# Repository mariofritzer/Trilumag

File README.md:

# Trilumag

Dreieckige RGBW-Lichtpanels zum Selberbauen, ähnlich wie Nanoleaf: Die Panels werden mit Magnet-Pogo-Steckern aneinandergeklipst, erkennen sich gegenseitig und erscheinen in der App genau so, wie sie an der Wand hängen. Gesteuert wird alles von einem ESP32 im Hauptpanel, per Web-App, HTTP-API und Home Assistant.

**Webinstaller:** https://mariofritzer.github.io/Trilumag/

## Stand

Aktuell: **Version 0.7**. Was sich wann geändert hat, steht im [Versionsverlauf](CHANGELOG.md).

Ab Version 0.2 gibt es zwei Betriebsarten, umschaltbar in der App: **Simulation** (Panels werden in der App per Ziehen angeklipst) und **Bus** (echte Panels über RS-485). Das Protokoll steht in [docs/protokoll.md](docs/protokoll.md).

| Teil | Stand |
| --- | --- |
| Firmware Hauptpanel (ESP32) | Simulation und echter Bus, Web-App im Stil von WLED mit fester Verbindung, Effekte mit Paletten, Presets, Pin-Einstellungen pro Board, MQTT mit Home-Assistant-Discovery, WLAN per Improv |
| Bus zu den Panels (RS-485) | Protokoll v1 fertig, am PC mit echter Firmware simuliert und getestet, Steckbrett-Test folgt |
| Firmware Panels (CH32V003) | Version 3: Erkennung, Farben, Kanten einzeln, Antippen per Bewegungssensor, Updates über den Bus mit eigenem Bootloader |
| Platinen | Entwurf v0.1 |

## Aufbau

- **Hauptpanel:** ESP32-S3, 24V-Eingang mit Sicherung und Verpolschutz, RS-485-Master, eigene LEDs
- **Panels:** CH32V003, RS-485, WS2814 24V RGBW (10 cm pro Kante)
- **Kanten:** je ein Paar Magnet-Pogo-Stecker (männlich + weiblich), 24V, GND, A, B und eine SNS-Leitung zur Nachbarerkennung
- **Kantennummerierung** bei jedem Panel gleich, gegen den Uhrzeigersinn: Kante 1 unten, 2 rechts, 3 links (Spitze oben)

## Ordner

| Ordner | Inhalt |
| --- | --- |
| `firmware/trilumag` | Arduino-Sketch für das Hauptpanel |
| `firmware/panel` | Firmware für die Panels (CH32V003, ch32fun) |
| `docs` | Bus-Protokoll |
| `installer` | Webinstaller-Seite (ESP Web Tools) |
| `.github/workflows` | baut die Firmware für ESP32, ESP32-S3, ESP32-C3 und ESP32-C6 und veröffentlicht den Installer |

## Selbst kompilieren

**Hauptpanel:** Arduino IDE mit dem Boardpaket **esp32** von Espressif, dazu die Bibliotheken **ArduinoJson** (ab 7), **PubSubClient** und **Adafruit NeoPixel**. Bei ESP32-S3, ESP32-C3 und ESP32-C6 unter Werkzeuge „USB CDC On Boot“ auf „Enabled“ stellen. Unter „Partition Scheme“ immer **Minimal SPIFFS (1.9MB APP with OTA)** wählen, sonst ist für Online-Updates kein Platz. Für den **ESP32-C6 mit Hue** zusätzlich „Zigbee mode“ auf **Zigbee ZCZR (coordinator/router)** stellen und `partitions_c6_zigbee.csv` als `partitions.csv` in den Sketch-Ordner kopieren (nur für diesen Build, sonst gilt sie für alle Chips). Die App steht in `webapp.h`; nach Änderungen daran `python3 .github/scripts/webapp_gz.py` ausführen, das erzeugt die gepackte Fassung `webapp_gz.h`, die das Hauptpanel ausliefert.

**Panels:** [ch32fun](https://github.com/cnlohr/ch32fun) und eine RISC-V-Toolchain. Ein neues Panel wird einmal mit dem WCH-LinkE programmiert: `make -C firmware/panel flashall CH32FUN=<pfad>/ch32fun/ch32fun` schreibt Bootloader, Option-Byte und Firmware. Danach bekommt es neue Versionen über den Bus vom Hauptpanel (Optionen → Panel-Firmware). Fertige Dateien gibt es bei jedem Release (`trilumag-panel.bin`, `trilumag-panel-bootloader.bin`).

## Web-App

Die App ist aufgebaut wie bei WLED: oben Ein/Aus und Gesamthelligkeit der ganzen Wand, unten fünf Tabs.

- **Farben:** Farbrad mit Helligkeit, Weißanteil, Schnellfarben und Hex-Eingabe. Ohne Auswahl gilt die Farbe für die ganze Wand. In der Vorschau oben angetippte Panels bekommen ihre eigene Farbe. Läuft ein Effekt, der eine Farbe benutzt, färbt das Farbrad den Effekt ein, statt ihn zu beenden.
- **Effekte:** Tempo, Intensität, Effektliste mit Suche und Paletten.
- **Wand:** Panels anordnen (in der Simulation per Ziehen), Details, Helligkeit und Ein/Aus pro Panel.
- **Presets:** Szenen speichern, abrufen und löschen (bis zu 16).
- **Optionen:** WLAN (gefundene Netze zum Antippen), Betriebsart, Board und Pins, Farbreihenfolge mit Farbtest, MQTT mit Schalter „MQTT aktiv“.

Die App hält wie WLED eine feste Verbindung (WebSocket auf Port 81). Das Hauptpanel schickt Änderungen und das Effektbild etwa 15-mal pro Sekunde von selbst. Ist die Verbindung weg, fragt die App per HTTP nach, bis sie wieder steht.

Updates über den Webinstaller behalten WLAN, Einstellungen, Farben und Presets. Nur „Gerät löschen“ beim Installieren setzt alles zurück.

## Android-App

Die App hat eine eigene Versionsnummer (1.0, 1.1, …), unabhängig von der Firmware; sie steigt nur, wenn sich an der App etwas ändert. Die Datei heißt `trilumag-app-<Version>.apk` und hängt an dem Release, mit dem diese App-Version kam: <https://github.com/mariofritzer/Trilumag/releases>. Beim ersten Installieren fragt Android, ob der Browser Apps installieren darf; das einmal erlauben.

- Beim Start sucht die App alle Trilumag im WLAN und zeigt sie als Liste mit Namen, Farbe, Ein/Aus-Schalter und Helligkeitsregler, ähnlich wie die WLED-App.
- Antippen öffnet die gewohnte Steuerung im Vollbild. ＋ fügt eine Wand über ihre IP-Adresse hinzu, langes Drücken entfernt sie aus der Liste.
- Die App sieht selbst bei GitHub nach (höchstens alle drei Stunden) und zeigt oben einen Hinweis, wenn eine neuere App-Version da ist. „Installieren“ lädt sie in der App herunter und installiert sie; dahinter wird alles unscharf, davor stehen Fortschritt und der aktuelle Schritt. Beim ersten Mal fragt Android, ob Trilumag Apps installieren darf.
- Sicherungen und das Wandbild werden unter Downloads gespeichert.
- **Hinweis bei Störung** (unten in der Liste einschalten): Die App sieht etwa alle 15 Minuten im Hintergrund nach, ob alle Panelwände erreichbar sind und ihre Panels antworten, und meldet sich sonst. Nur im eigenen WLAN, unterwegs kommt nichts.

## Effekte und Paletten

Effekte laufen immer über die ganze Wand: Einfarbig, Regenbogen, Regenbogenwelle, Atmen, Farbwechsel, Funkeln, Ausbreiten (Wellen vom Hauptpanel nach außen), Feuer und Polarlicht. Die **Intensität** ändert je nach Effekt die Streuung, die Tiefe des Atmens, wie oft es funkelt, die Breite der Wellen oder wie stark das Feuer flackert.

**Paletten:** Standard (die eigenen Farben des Effekts), Regenbogen, Effektfarbe, Ozean, Lava, Wald, Sonnenuntergang, Party, Pastell und Eis.

Das Hauptpanel rechnet die Bilder selbst und schickt etwa 25 pro Sekunde mit einem FRAME-Befehl an alle Panels. Neu angeklipste Panels pulsieren erst 5-mal blau (etwa 8 Sekunden) und laufen dann mit. Bekommt ein einzelnes Panel eine feste Farbe, endet der Effekt. Der zuletzt gewählte Effekt läuft nach einem Neustart weiter.

## Presets

Ein Preset merkt sich Ein/Aus, Gesamthelligkeit, den Effekt mit Tempo, Intensität, Palette und Effektfarbe und die Farbe jedes bekannten Panels über seine Chip-ID. Ist ein Panel beim Laden gerade nicht an der Wand, bekommt es seine Farbe beim nächsten Anklipsen.

## Home Assistant

In der App unter Optionen „MQTT aktiv“ einschalten und die Adresse des Brokers eintragen. Danach erscheinen automatisch:

- **Ein Licht pro Panel**
- **„Alle Panels“:** Ein/Aus, Gesamthelligkeit, Farbe und die Effektliste.
- **Schieberegler:** „Effekt-Tempo“ und „Effekt-Intensität“.
- **Auswahlen:** „Palette“ und „Preset“.
- **Status** (Diagnose): „Bereit“ oder „Update läuft“. Während die Wand eine neue Firmware installiert, trennt sie alle Verbindungen nach außen (MQTT, Hue, WLED, Wetter, Suche nach anderen Wänden) und verbindet sich nach dem Neustart von selbst wieder.

## Signale und Fortschritt (Home Assistant)

- **Signal:** Das Gerät „Signal“ (notify) lässt die ganze Wand blinken, danach läuft alles weiter wie vorher, auch ein Effekt. Nachricht: Farbe und Anzahl, z. B. `blau 3` oder `#ff8800 5`. Farben: rot, grün, blau, gelb, orange, lila, pink, türkis, weiß.

  ```yaml
  action: notify.send_message
  target: {entity_id: notify.trilumag_signal}
  data: {message: "blau 3"}
  ```

  Per MQTT geht auch JSON an `trilumag/signal/set`: `{"color":"grün","blink":2,"ms":700}`.
- **Fortschritt:** Die Zahl „Fortschritt“ (0 bis 100 %) füllt die Wand vom Hauptpanel aus, 0 % schaltet es aus. Mit Farbe per MQTT an `trilumag/fortschritt/set`: `{"value":40,"color":"grün"}`.

## Mehrere Wände

Unter Optionen → Mehrere Wände lassen sich Wände im selben WLAN zu einer Gruppe (1 bis 9) verbinden. Sie teilen Ein/Aus, Helligkeit und Effekt mit allen Einstellungen, egal an welcher Wand man etwas ändert. Den Takt der Effekte gibt die Wand mit der kleinsten Chip-ID vor. Feste Farben einzelner Panels bleiben pro Wand.

## Energie

Trilumag zählt den Verbrauch mit, gemessen mit dem INA226 oder aus den Farben geschätzt, und zeigt ihn unter Optionen → Energie pro Tag, Monat und Jahr. Das Datum kommt per Internet (NTP, Zeitzone Österreich). In Home Assistant gibt es den Zähler „Energie“ (kWh) für das Energie-Dashboard.

## WLAN-Wächter und Neustart-Grund

Unter Optionen → WLAN lässt sich der WLAN-Wächter ein- und ausschalten (Standard: an). Ist das WLAN 3 Minuten weg, verbindet sich Trilumag neu; fehlt es nach 10 Minuten immer noch, startet es neu, außer jemand ist gerade im Setup-Netz. Hängt die Hauptschleife eine Minute, startet es ebenfalls neu. `trilumag.local` wird alle 30 Minuten neu angekündigt. Warum Trilumag zuletzt neu gestartet ist (Stromausfall, Update, Absturz, Wächter …) und wie oft es abgestürzt ist, steht unter Optionen → Info und im Ereignisprotokoll.

## Andere Trilumag im WLAN

Unter Optionen → Andere Trilumag sucht die App nach weiteren Wänden im selben WLAN (per mDNS) und listet sie mit Name, Adresse und Version auf. „Öffnen“ führt direkt zu deren Steuerungsseite. Laufen mehrere Wände, heißt nur eine davon `trilumag.local`, die anderen bekommen automatisch `trilumag-2.local` und so weiter; die Liste zeigt, welche welche ist.

Unter Optionen → Updates lässt sich dann auswählen, auf welchen Wänden eine Version installiert wird: diese Wand und/oder gefundene andere. Die anderen holen sich die Version selbst von GitHub; ist diese Wand auch dabei, kommt sie zuletzt dran. Wände ab 0.7.21 lassen sich so aktualisieren.

## Raum: mehrere Panelwände zusammen

Begriffe: Eine **Panelwand** ist ein Trilumag mit seinen Panels, eine **Raumwand** eine Wand des Raums im Grundriss.

Unter Optionen → Andere Trilumag → „Raum einrichten“ (in der Android-App über ⌂ oben):

- **Grundriss von oben:** Ecken ziehen, ＋ an einer Raumwand fügt eine Ecke ein, eine Ecke oder Raumwand antippen zum Löschen. Die Panelwände (Striche) zieht man entlang der Raumwände an ihren Platz.
- **Jede Raumwand von vorne:** so, wie man im Raum davor steht, mit den echten Panel-Formen und ihren aktuellen Farben. Panelwände frei an ihre Stelle und Höhe ziehen.
- **Maße:** Raumhöhe und Seitenlänge eines Panels in cm.
- Der Raum liegt auf allen Panelwänden gleich: wo man ihn ändert, wird er an alle anderen weitergegeben. Klipst man an einer Panelwand Panels ab oder an, zieht sie ihren Eintrag selbst nach.
- **Raum-Effekte:** Der Raum-Komet läuft wie der Komet einer Panelwand: Panel für Panel, bei „Kanten einzeln“ Kante für Kante, und springt am Ende einer Panelwand zur nächsten Panelwand im Raum. Es gibt genau einen Kopf für alle Panelwände. Raum-Regenbogen und Raum-Welle laufen entlang der Raumwände über alle Panelwände. Jede Panelwand rechnet selbst mit ihrer Stelle im Raum und der Uhrzeit aus dem Internet, es werden keine Bilder verschickt. Lange Lücken zwischen den Panelwänden werden dabei kurz. Helligkeit, Tempo, Intensität und Palette gehen an alle Panelwände, eigene Paletten mit ihren Farben.
- **Mehrere Räume** (bis zu 6): oben im Raum-Fenster umschalten, „＋ Raum“ legt einen neuen an, der Name steht unter „Maße“. Eine Panelwand steht in höchstens einem Raum; „Hierher holen“ holt sie aus einem anderen.
- **Raum löschen:** löscht diesen Raum mit Grundriss, Aufstellung und Szenen auf allen Panelwänden; die Panelwände und ihre Einstellungen bleiben.
- **Raum-Szenen:** merken sich, was jede Panelwand im Raum zeigt (Effekt, Farben, Helligkeit), und stellen es auf allen wieder her (bis zu 8 je Raum).
- **Antippen:** Steht die Panelwand in einem Raum, läuft die Welle beim Antippen über alle Panelwände des Raums.
- **Home Assistant:** Jeder Raum erscheint als eigenes Licht (Ein/Aus, Helligkeit, alle Effekte inkl. Raum-Effekte) für alle seine Panelwände.
- **Weitere Raum-Effekte:** Raum-Feuerwerk (Raketen explodieren an Panels im ganzen Raum), Raum-Pingpong (ein Lichtpunkt springt zwischen den Panelwänden hin und her), Raum-Atmen (Atmen als Welle von der Mitte durch den Raum).
- Die anderen Panelwände brauchen dafür mindestens dieselbe Version.

Auch der Gleichtakt (unter „Mehrere Panelwände“) nimmt jetzt eigene Paletten mit ihren Farben mit; die andere Panelwand legt sie als „mitgenommene“ Palette ab, ohne ihre eigenen zu ändern.

## Weißton und Tageslicht-Kurve

Im Tab Farben stellt der Regler „Weißton“ Weiß zwischen 2200 K (warm) und 6500 K (kalt) ein; Home Assistant bekommt dafür den Farbtemperatur-Modus. Unter Optionen → Licht macht die „Tageslicht-Kurve“ alle Farben und Effekte abends wärmer und dunkler (ab 18 Uhr, nachts ganz warm auf 35 %, ab 6 Uhr wieder hell). Die Uhrzeit kommt per Internet.

## Eigene Paletten

Im Tab Effekte unter „Eigene Paletten“ lassen sich bis zu 4 Paletten mit 2 bis 6 Farben anlegen (als Vorlage gibt es „Rot-Gold-Weiß“). Sie stehen in der Palettenliste, in Home Assistant und in Presets wie die eingebauten.

## Wetter

Der Effekt „Wetter“ zeigt die Außentemperatur als Farbe (blau = kalt, gelb = mild, rot = heiß), bei Regen laufen blaue Tropfen über die Wand, bei Schnee weiße. Den Ort trägst du unter Optionen → Wetter ein; die Daten kommen alle 15 Minuten von Open-Meteo, kostenlos und ohne Anmeldung.

## Spiel „Simon sagt“

Unter Wand → Spiel startet ein Merkspiel: Die Wand zeigt eine Folge von Panels, man tippt sie nach, jede Runde kommt eines dazu. Dafür muss „Panels reagieren auf Antippen“ an sein, und es braucht mindestens zwei Panels mit Sensor. Der Rekord wird gespeichert.

## WLED nachahmen

Unter Optionen → WLED nachahmen findet die App WLED-Geräte im WLAN (oder man gibt die IP ein). Trilumag fragt das Gerät alle 1,5 s ab und übernimmt Änderungen an Ein/Aus, Helligkeit, Farbe, Tempo und Intensität, dazu den Effekt, wenn es ein Gegenstück gibt (etwa Rainbow, Breathe, Fire 2012, Aurora, Sparkle, Meteor, Lightning, Fireworks).

## Hue-Lampe nachahmen

Unter Optionen → Hue-Lampe nachahmen folgt die Wand einer Lampe der Hue Bridge (geht mit jedem Chip, übers WLAN): Bridge suchen, den runden Knopf auf der Bridge drücken und „Koppeln“ tippen, dann eine Lampe wählen. Trilumag fragt die Lampe jede Sekunde über die lokale Schnittstelle der Bridge (API v2) ab und übernimmt Ein/Aus, Helligkeit, Farbe, Weißton und die Effekte Kerze, Feuer, Funkeln, Prisma und Opal.

## Störungsanzeige

Ist das WLAN weg oder antwortet ein Panel nicht mehr, blinkt das Hauptpanel alle 10 Sekunden zweimal kurz (orange bzw. rot), solange die Wand an ist. Abschaltbar unter Optionen → WLAN.

## Wand als Bild

Unter Wand → „Wand als Bild speichern“ entsteht ein PNG mit den aktuellen Farben, Panelnummern, Chip-IDs, der Ausrichtung (Punkt = Kante 1) und den Datenverbindungen.

## Panel tauschen

In der App unter Wand das Panel antippen und „Tauschen“ wählen. Danach bleiben 5 Minuten Zeit: das alte Panel abklipsen und das neue an genau dieselbe Stelle setzen. Das neue übernimmt Farbe, Helligkeit und „Kanten einzeln“ des alten. Solange läuft unten in der App ein kleines Fenster mit der Restzeit und ✕ zum Abbrechen. Panels, die hinter dem alten hingen, gehen beim Abklipsen kurz aus und melden sich über das neue wieder; in der Simulation landen sie dazwischen in der Ablage und kommen danach von selbst an ihren Platz zurück.

## Sprache

Die App ist auf Deutsch und Englisch. Sie richtet sich nach der Sprache des Browsers; unter Optionen → Name lässt sie sich fest einstellen. Die Namen in Home Assistant und die Versionshinweise bleiben deutsch.

## Philips Hue (nur ESP32-C6)

Mit einem ESP32-C6 als Hauptpanel meldet sich Trilumag zusätzlich als Zigbee-3.0-Farblampe „Trilumag Wand“. Eine Hue Bridge (auch die Bridge Pro) nimmt sie wie eine Lampe eines anderen Herstellers auf: Ein/Aus, Helligkeit und Farbe der ganzen Wand, auch in Szenen, Routinen und mit Hue-Schaltern. Effekte und einzelne Panels bleiben in der Trilumag-App.

- Einschalten unter Optionen → Philips Hue, dann in der Hue-App unter Einstellungen → Lampen → „+“ nach neuen Lampen suchen.
- Der C6 braucht dafür einmal die neue Speicheraufteilung mit den Zigbee-Bereichen: einmal mit dem Webinstaller flashen. Einstellungen und Wand bleiben erhalten.
- WLAN und Zigbee teilen sich beim C6 eine Antenne. Hängt das Hauptpanel mit Zigbee dreimal beim Start, schaltet es Zigbee von selbst wieder aus.
- Alle anderen Chips haben kein Zigbee, dort fehlt das Kästchen in der App.

## API

| Aufruf | Zweck |
| --- | --- |
| `GET /api/state` | alle Panels mit Position, Drehung und Farbe, dazu Ein/Aus, Gesamthelligkeit, Effekt, Effekte, Paletten und Presets |
| `POST /api/set` | ein Panel: `{"id":"A3F2C1D0","state":"ON","brightness":180,"color":{"r":255,"g":0,"b":0,"w":0}}`, mehrere: `{"ids":[…],…}`, ganze Wand: `{"id":"alle","state":"ON","brightness":200,"color":{…}}` (hier ist `brightness` die Gesamthelligkeit), Helligkeit aller Panels: `{"panelBri":255}`, Weißton: `"kelvin":2700` statt `color` |
| `POST /api/effect` | `{"effect":"welle","speed":50,"intensity":128,"palette":"ozean","direction":90,"spin":0}`, alle Felder optional, `"aus"` heißt Einfarbig. Beim Farbverlauf (`"verlauf"`) setzt `"color2":{"r":0,"g":80,"b":255,"w":0}` die zweite Farbe |
| `POST /api/presets` | `{"action":"save","name":"Abend"}`, `{"action":"load","id":0}`, `{"action":"delete","id":0}` |
| `GET /api/live` | aktuelles Effektbild aller Panels als RRGGBBWW |
| `GET /api/diag` | Bus-Diagnose: Zähler, Antwortzeiten pro Panel, Ereignisprotokoll |
| `GET /api/backup`, `POST /api/restore` | Sicherung herunterladen und einspielen |
| `POST /api/light` | Übergangszeit, Stromlimit und Stromsensor-Pins |
| `POST /api/touch` | Antippen: an/aus, Empfindlichkeit 1–10, Aktion für einmal (`a1`) und doppelt (`a2`) |
| `POST /api/signal` | Signal: `{"color":"blau","blink":3,"ms":700}` |
| `POST /api/progress` | Fortschritt: `{"value":40,"color":"grün"}`, `0` = aus |
| `POST /api/identify` | Panel finden: `{"id":"…"}`, das Panel blinkt 3 s weiß |
| `POST /api/favs` | Favoriten: `{"effect":"lava","on":true}` |
| `POST /api/swap` | Panel tauschen: `{"id":"altes Panel"}` startet, danach 5 Minuten Zeit; `{"stop":true}` bricht ab |
| `POST /api/ota` | Updates: `{"action":"check"}`, `{"action":"install","version":"0.7.40"}`, auch für andere Wände: `"peers":["192.168.1.61"]`, ohne diese Wand: `"self":false` |
| `POST /api/peers`, `GET /api/peers` | andere Trilumag im WLAN suchen (dauert etwa 3 s) und die Liste abholen |
| `POST /api/palette` | Eigene Palette: `{"action":"save","slot":0,"name":"Rot-Gold-Weiß","colors":["#FF0000","#FFB000","#FFFFFF"]}`, `{"action":"delete","slot":0}` |
| `POST /api/weather` | Wetter: `{"place":"Wien"}` (Ort suchen und Wetter holen), `{"place":""}` löscht ihn |
| `POST /api/game` | Spiel „Simon sagt“: `{"action":"start"}` / `{"action":"stop"}` |
| `POST /api/hue`, `GET /api/hue` | Hue-Lampe nachahmen: `{"action":"find"}`, `{"action":"pair"}`, `{"action":"lights"}`, `{"action":"follow","id":"…","name":"…"}`, `{"action":"stop"}`, `{"action":"forget"}`; GET liefert Bridges und Lampen |
| `POST /api/mirror` | WLED nachahmen: `{"ip":"192.168.1.70"}`, `{"ip":""}` beendet es |
| `POST /api/fault` | Störungsanzeige: `{"on":true}` |
| `POST /api/guard` | WLAN-Wächter: `{"on":true}` |
| `POST /api/sleep` | Sleep-Timer: `{"min":30}`, `0` beendet ihn |
| `POST /api/boot` | Nach Stromausfall: `{"mode":0}` wie vorher, `1` aus, `2` an, `3` mit `"preset"` |
| `GET /api/energy` | Energieverbrauch: heute, Monat, Jahr, gesamt und Werte pro Tag, Monat und Jahr (Wh) |
| `POST /api/sync` | Mehrere Wände im Gleichtakt: `{"on":true,"group":1}` (UDP-Port 21330 im WLAN) |
| `POST /api/zigbee` | Nur ESP32-C6: `{"action":"on","value":true}` (startet neu), `{"action":"pair"}` (neu koppeln) |
| `POST /api/panelfw` | Panel-Firmware: `{"action":"all"}`, `{"action":"one","id":"…"}`, `{"action":"auto","on":true}` |
| `/json`, `/json/state`, `/json/info`, `/presets.json` | WLED-kompatible Schnittstelle (eine Wand = ein Segment) |
| `POST /api/sim/attach` | Simulation: Panel anklipsen |
| `POST /api/sim/detach` | Simulation: Panel abklipsen |
| `POST /api/sim/rotate` | Simulation: Panel an Ort und Stelle drehen, `{"id":"…"}` |
| `POST /api/sim/remove` | Simulation: Panel aus der Ablage löschen, `{"id":"…"}` oder `{"all":true}` |

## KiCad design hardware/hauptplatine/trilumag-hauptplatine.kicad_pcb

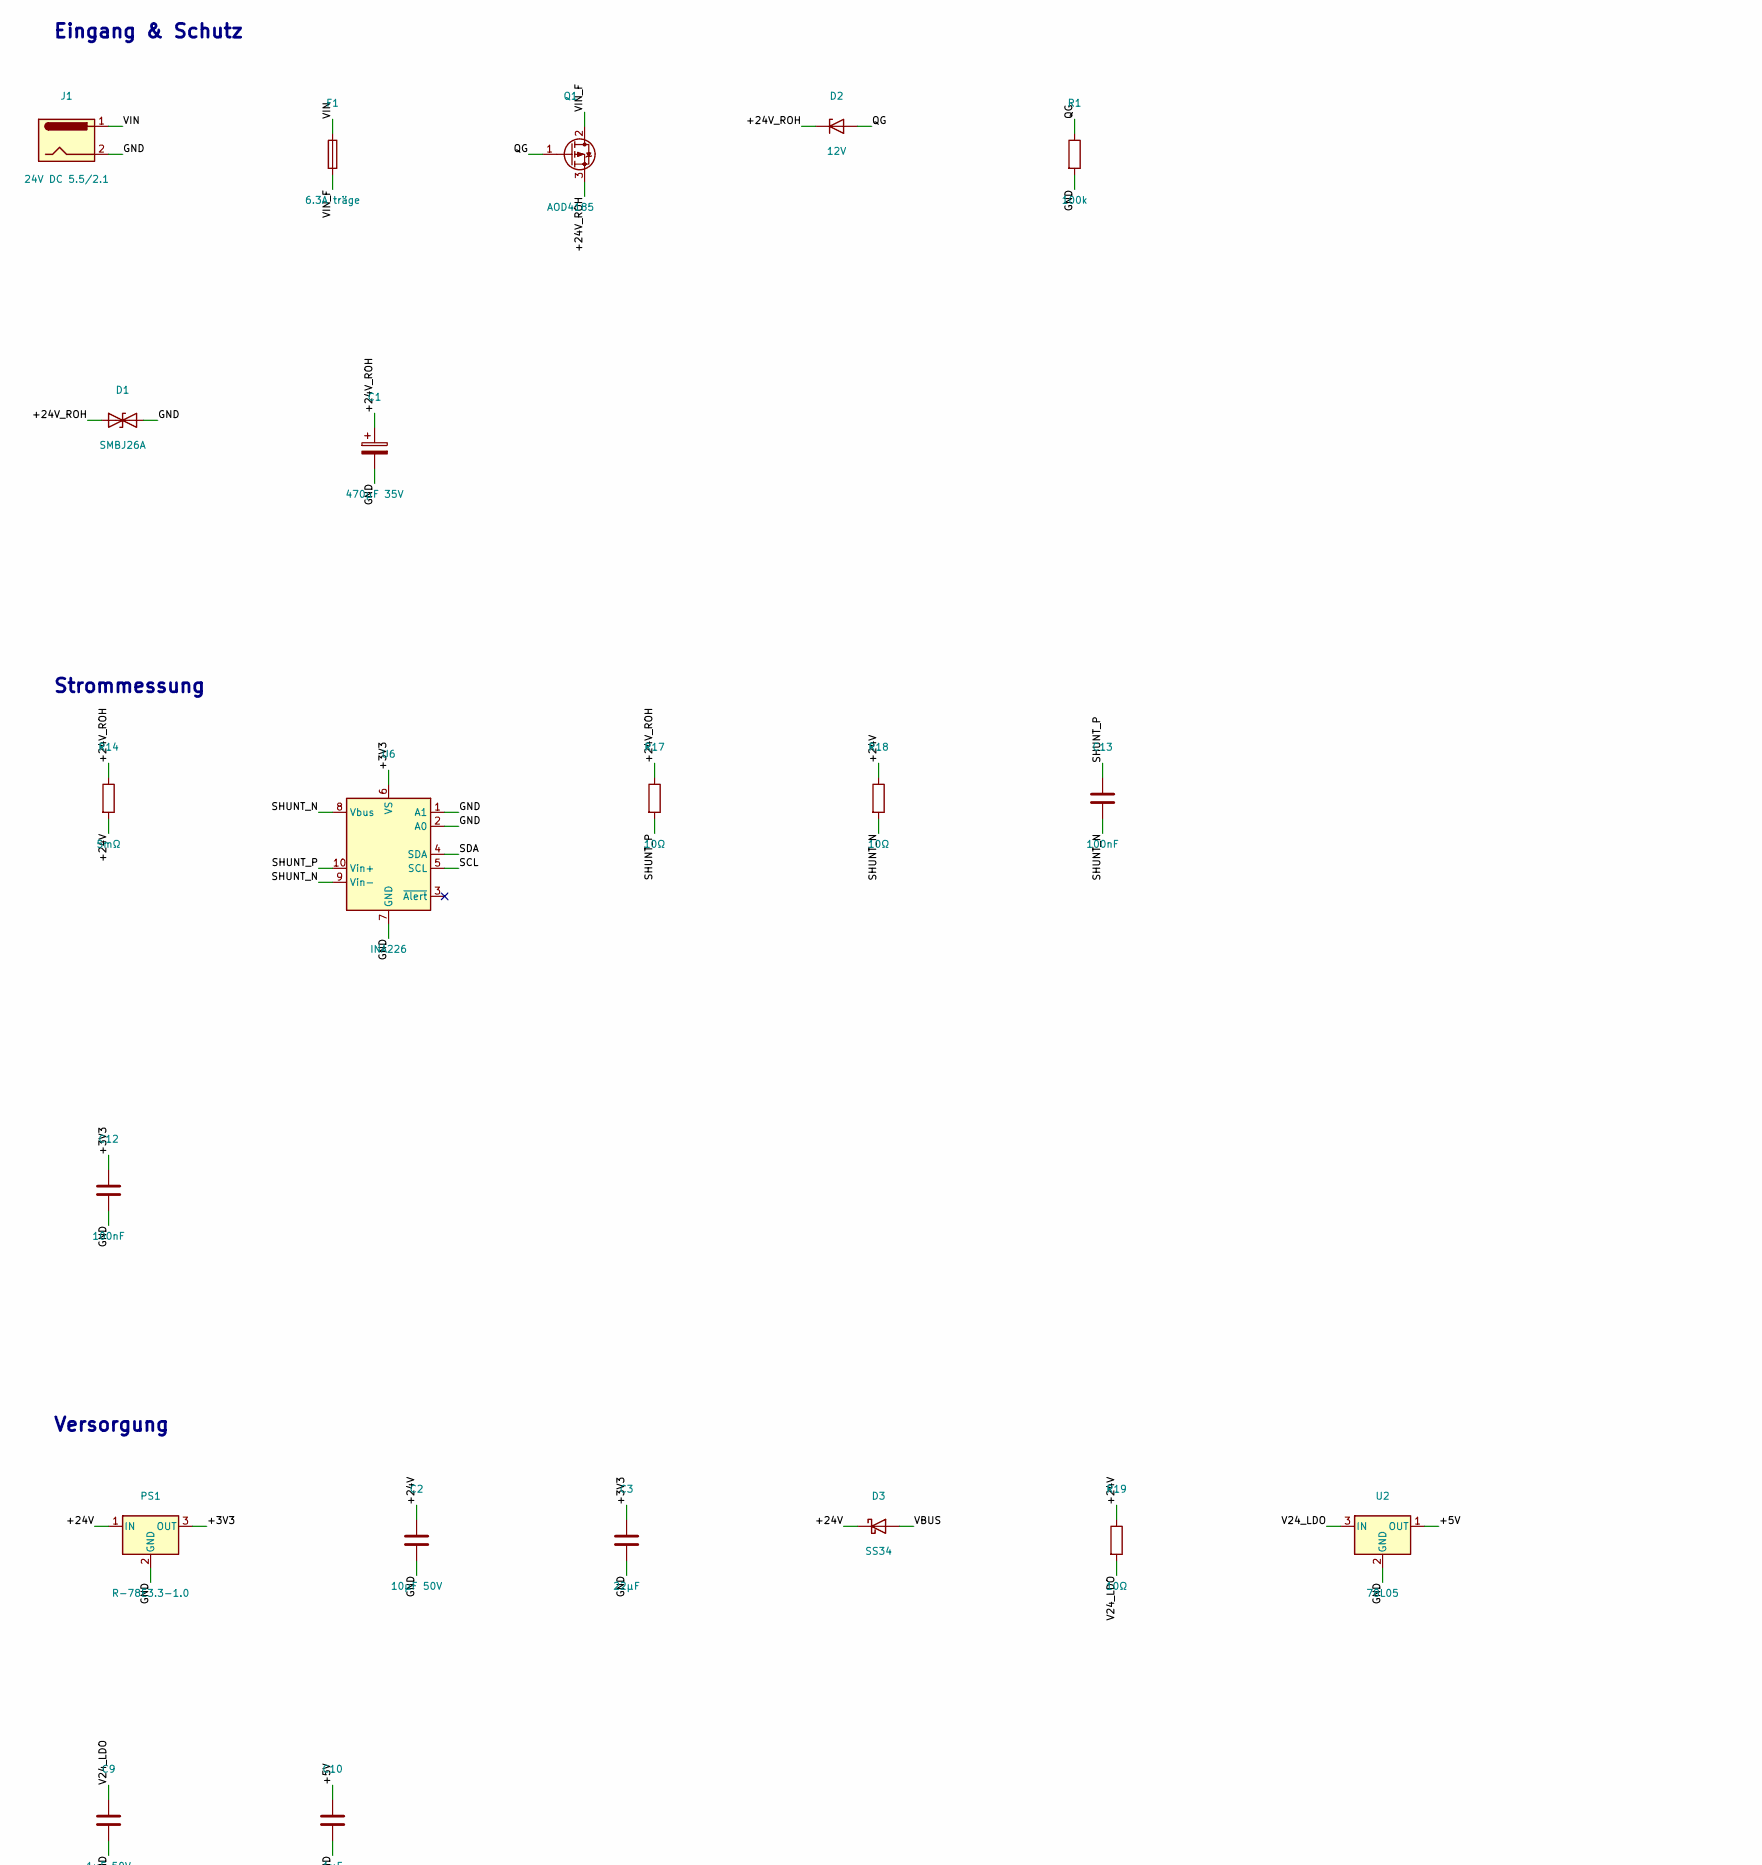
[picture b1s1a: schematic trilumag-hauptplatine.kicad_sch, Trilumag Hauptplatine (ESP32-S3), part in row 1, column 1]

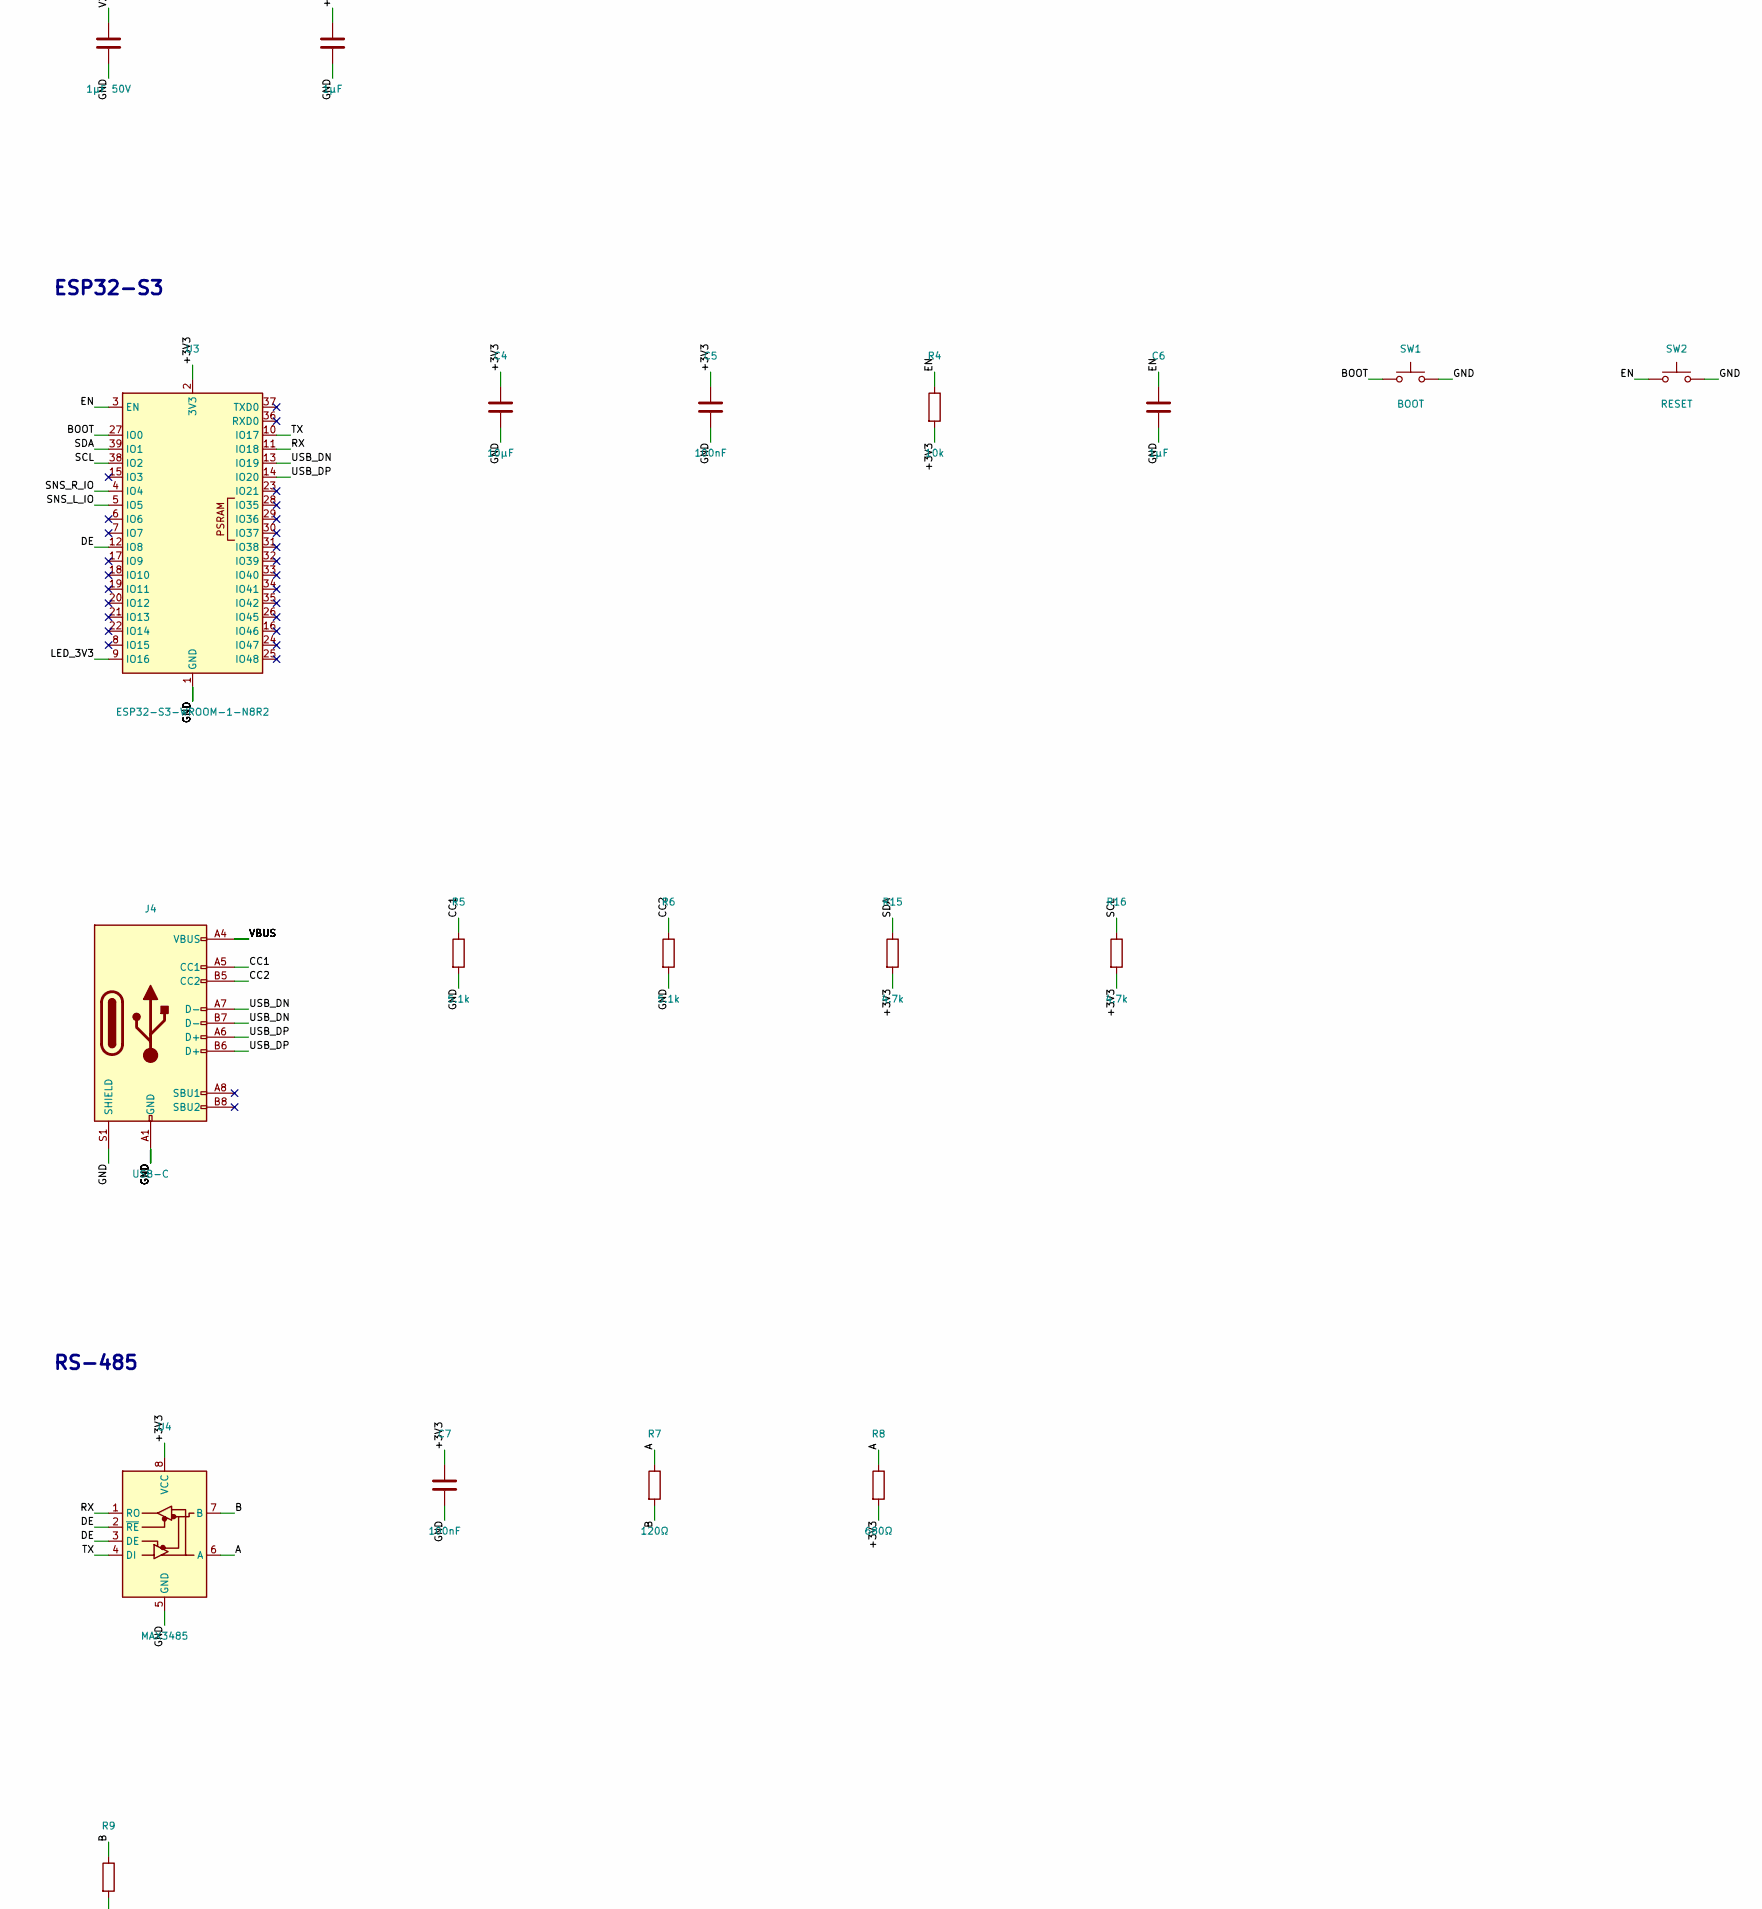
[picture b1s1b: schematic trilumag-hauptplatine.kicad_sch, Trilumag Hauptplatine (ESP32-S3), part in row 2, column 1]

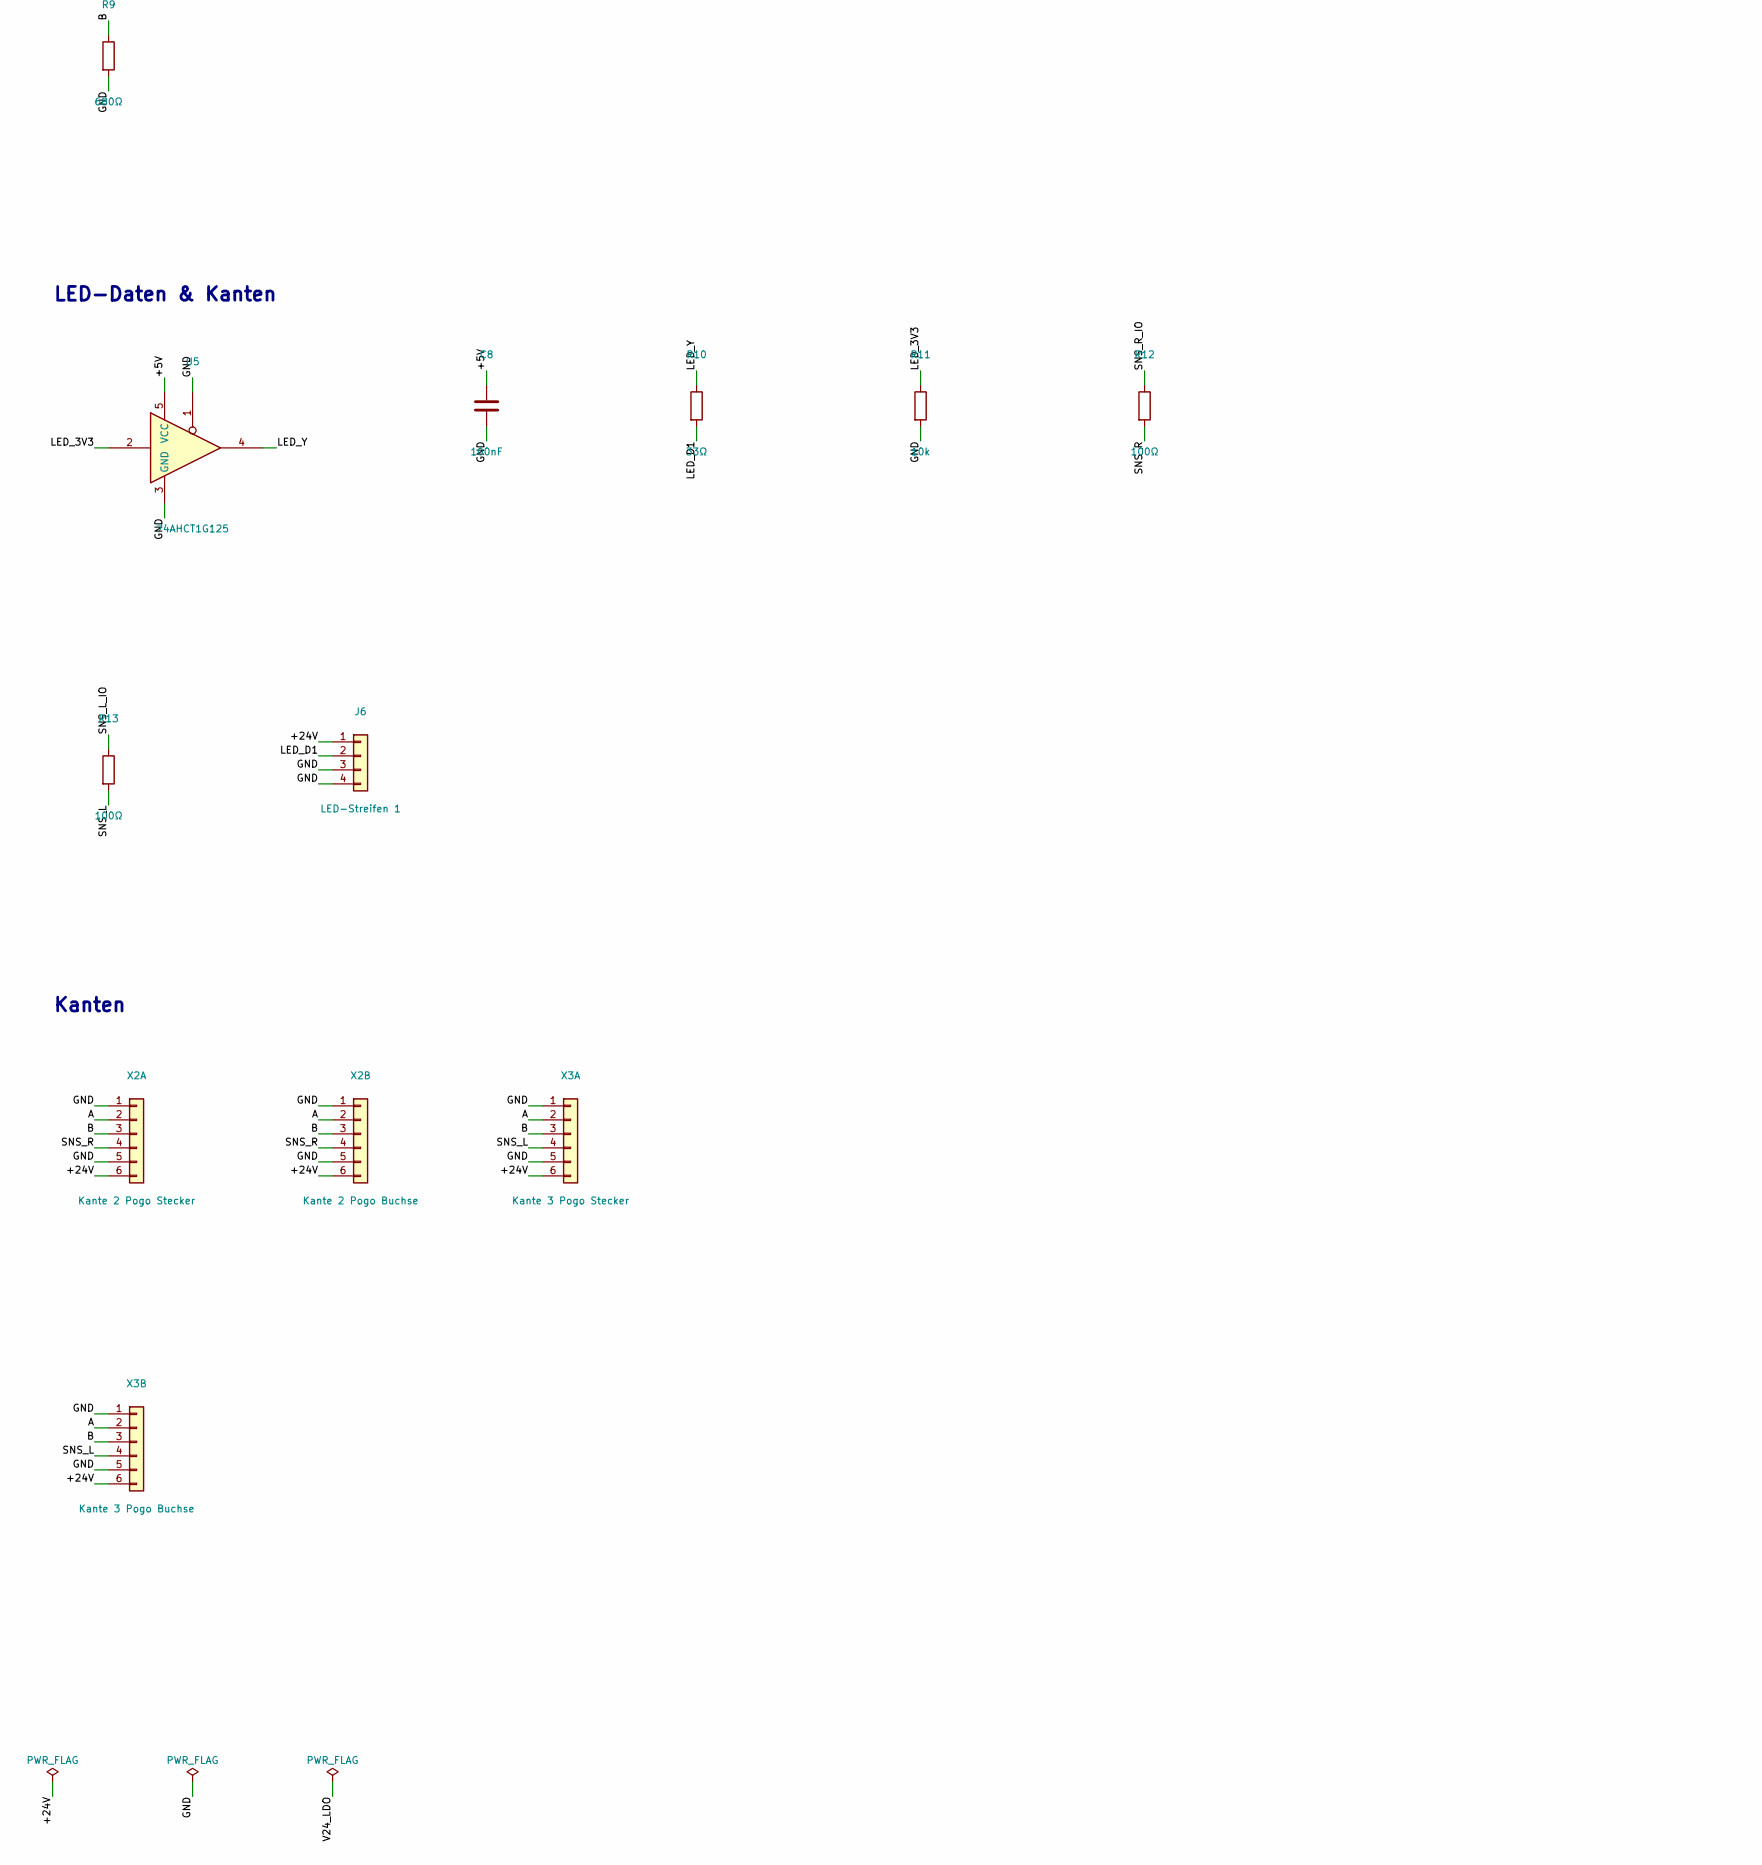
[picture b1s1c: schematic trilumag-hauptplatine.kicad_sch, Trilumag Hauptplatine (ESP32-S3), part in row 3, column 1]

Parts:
C1: 470µF 35V; CP_Elec_10x10.5
C2: 10µF 50V; C_1206_3216Metric_Pad1.33x1.80mm_HandSolder
C3: 22µF; C_1206_3216Metric_Pad1.33x1.80mm_HandSolder
C4: 10µF; C_0805_2012Metric_Pad1.18x1.45mm_HandSolder
C5, C7, C8, C12, C13: 100nF; C_0805_2012Metric_Pad1.18x1.45mm_HandSolder
C6, C10: 1µF; C_0805_2012Metric_Pad1.18x1.45mm_HandSolder
C9: 1µF 50V; C_0805_2012Metric_Pad1.18x1.45mm_HandSolder
D1: SMBJ26A; D_SMB_Handsoldering
D2: 12V; D_SOD-123
D3: SS34; D_SMA_Handsoldering
F1: 6.3A träge; Fuseholder_Clip-5x20mm_Bel_FC-203-22_Lateral_P17.80x5.00mm_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
J1: 24V DC 5.5/2.1; BarrelJack_Horizontal
J4: USB-C; USB_C_Receptacle_GCT_USB4105-xx-A_16P_TopMnt_Horizontal
J6: LED-Streifen 1; Kabel_4P_LED
PS1: R-78E3.3-1.0; Converter_DCDC_RECOM_R-78E-0.5_THT
Q1: AOD4185; TO-252-2
R1: 100k; R_0805_2012Metric_Pad1.20x1.40mm_HandSolder
R4, R11: 10k; R_0805_2012Metric_Pad1.20x1.40mm_HandSolder
R5, R6: 5.1k; R_0805_2012Metric_Pad1.20x1.40mm_HandSolder
R7: 120Ω; R_0805_2012Metric_Pad1.20x1.40mm_HandSolder
R8, R9: 680Ω; R_0805_2012Metric_Pad1.20x1.40mm_HandSolder
R10: 33Ω; R_0805_2012Metric_Pad1.20x1.40mm_HandSolder
R12, R13: 100Ω; R_0805_2012Metric_Pad1.20x1.40mm_HandSolder
R14: 5mΩ; R_2512_6332Metric_Pad1.40x3.35mm_HandSolder
R15, R16: 4.7k; R_0805_2012Metric_Pad1.20x1.40mm_HandSolder
R17, R18: 10Ω; R_0805_2012Metric_Pad1.20x1.40mm_HandSolder
R19: 10Ω; R_1206_3216Metric_Pad1.30x1.75mm_HandSolder
SW1: BOOT; SW_PUSH_6mm
SW2: RESET; SW_PUSH_6mm
U2: 78L05; SOT-89-3_Handsoldering
U3: ESP32-S3-WROOM-1-N8R2; ESP32-S3-WROOM-1
U4: MAX3485; SOIC-8_3.9x4.9mm_P1.27mm
U5: 74AHCT1G125; SOT-23-5_HandSoldering
U6: INA226; VSSOP-10_3x3mm_P0.5mm
X2A: Kante 2 Pogo Stecker; Kabel_6P_Stecker
X2B: Kante 2 Pogo Buchse; Kabel_6P_Buchse
X3A: Kante 3 Pogo Stecker; Kabel_6P_Stecker
X3B: Kante 3 Pogo Buchse; Kabel_6P_Buchse

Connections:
+3V3: C3.1, C4.1, C5.1, C7.1, C12.1, PS1.3 (OUT), R4.2, R8.2, R15.2, R16.2, U3.2 (3V3), U4.8 (VCC), U6.6 (VS)
+5V: C8.1, C10.1, U2.1 (OUT), U5.5 (VCC)
+24V: C2.1, D3.1 (K), J6.1, PS1.1 (IN), R14.2, R18.1, R19.1, X2A.6, X2B.6, X3A.6, X3B.6
+24V_ROH: C1.1, D1.1 (A1), D2.1 (K), Q1.3 (S), R14.1, R17.1
A: R7.1, R8.1, U4.6 (A), X2A.2, X2B.2, X3A.2, X3B.2
B: R7.2, R9.1, U4.7 (B), X2A.3, X2B.3, X3A.3, X3B.3
BOOT: SW1.1, U3.27 (IO0)
CC1: J4.A5 (CC1), R5.1
CC2: J4.B5 (CC2), R6.1
DE: U3.12 (IO8), U4.2 (~RE), U4.3 (DE)
EN: C6.1, R4.1, SW2.1, U3.3 (EN)
GND: C1.2, C2.2, C3.2, C4.2, C5.2, C6.2, C7.2, C8.2, C9.2, C10.2, C12.2, D1.2 (A2), J1.2, J1.3, J4.A1 (GND), J4.A12 (GND), J4.B1 (GND), J4.B12 (GND), J4.S1 (SHIELD), J6.3, J6.4, PS1.2 (GND), R1.2, R5.2, R6.2, R9.2, R11.2, SW1.2, SW2.2, U2.2 (GND), U3.1 (GND), U3.40 (GND), U3.41 (GND), U4.5 (GND), U5.1, U5.3 (GND), U6.1 (A1), U6.2 (A0), U6.7 (GND), X2A.1, X2A.5, X2B.1, X2B.5, X3A.1, X3A.5, X3B.1, X3B.5; also elsewhere on the board
LED_3V3: R11.1, U3.9 (IO16), U5.2
LED_D1: J6.2, R10.2
LED_Y: R10.1, U5.4
QG: D2.2 (A), Q1.1 (G), R1.1
RX: U3.11 (IO18), U4.1 (RO)
SCL: R16.1, U3.38 (IO2), U6.5 (SCL)
SDA: R15.1, U3.39 (IO1), U6.4 (SDA)
SHUNT_N: C13.2, R18.2, U6.8 (Vbus), U6.9 (Vin-)
SHUNT_P: C13.1, R17.2, U6.10 (Vin+)
SNS_L: R13.2, X3A.4, X3B.4
SNS_L_IO: R13.1, U3.5 (IO5)
SNS_R: R12.2, X2A.4, X2B.4
SNS_R_IO: R12.1, U3.4 (IO4)
TX: U3.10 (IO17), U4.4 (DI)
USB_DN: J4.A7 (D-), J4.B7 (D-), U3.13 (IO19)
USB_DP: J4.A6 (D+), J4.B6 (D+), U3.14 (IO20)
V24_LDO: C9.1, R19.2, U2.3 (IN)
VBUS: D3.2 (A), J4.A4 (VBUS), J4.A9 (VBUS), J4.B4 (VBUS), J4.B9 (VBUS)
VIN: F1.1, J1.1
VIN_F: F1.2, Q1.2 (D)

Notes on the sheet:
Eingang & Schutz
Strommessung
Versorgung
ESP32-S3
RS-485
LED-Daten & Kanten
Kanten

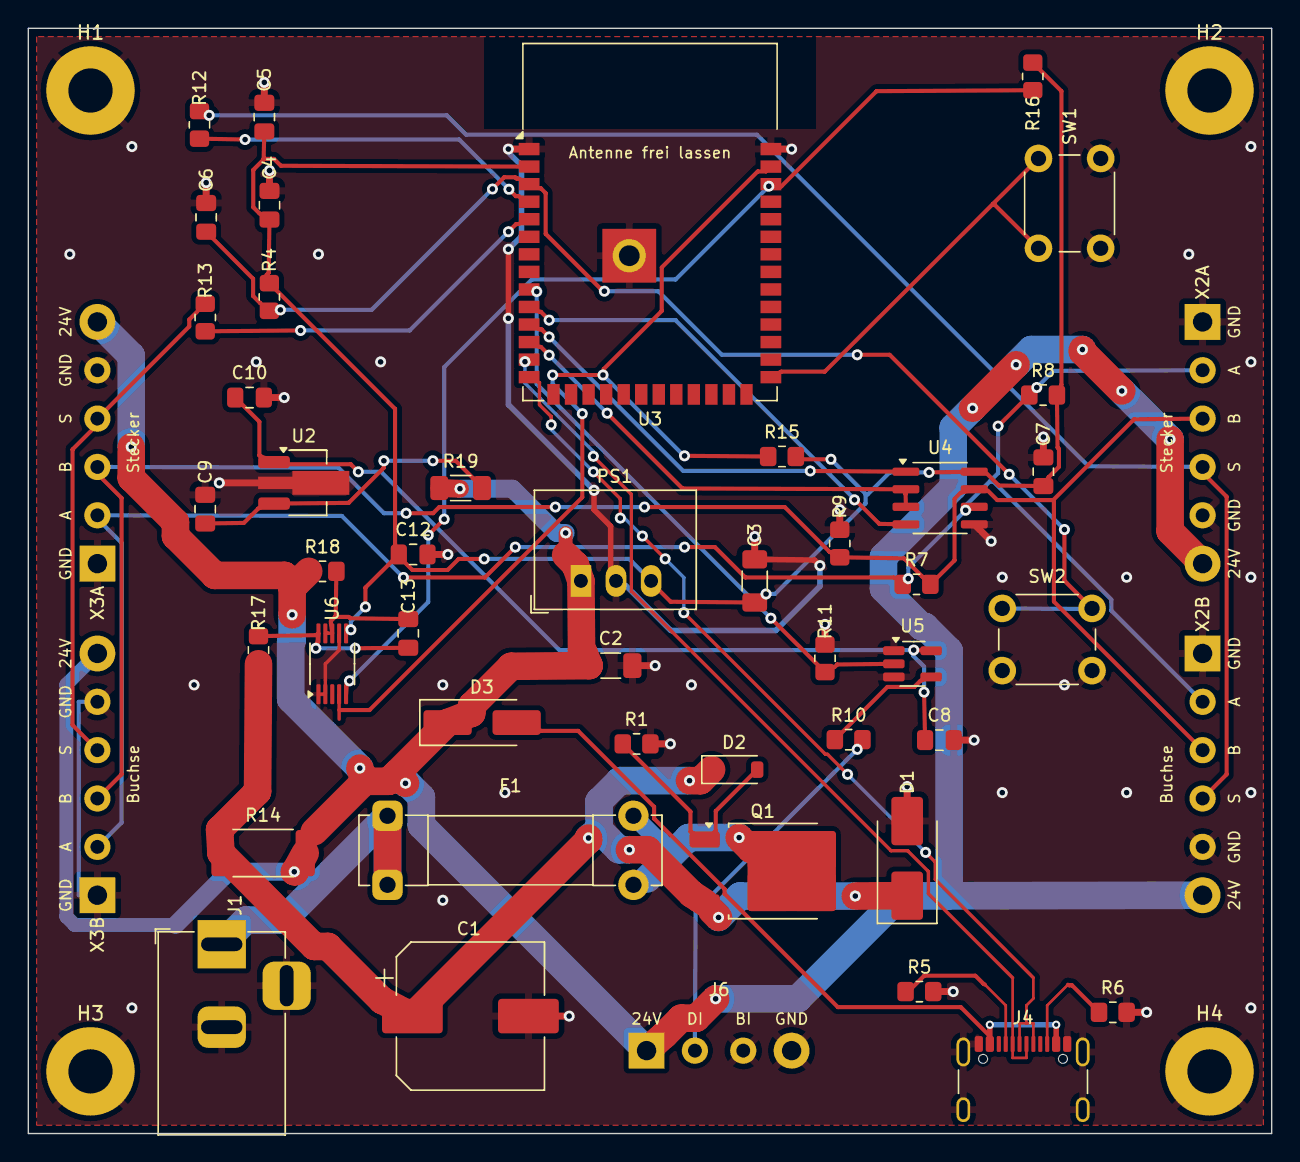
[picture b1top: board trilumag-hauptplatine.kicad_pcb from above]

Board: 2 copper layers, 90.0 x 80.0 mm, 53 parts (0 on the bottom side), 32 nets.

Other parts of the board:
H1, H2, H3, H4: M3; MountingHole_3.2mm_M3_Pad

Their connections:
GND: H1.1, H2.1, H3.1, H4.1; also elsewhere on the board

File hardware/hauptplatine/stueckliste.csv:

Menge;Referenzen;Wert;Footprint;Bestellhinweis
1;C1;470µF 35V;CP_Elec_10x10.5;Elko SMD 10×10,5 470 µF 35 V
1;C2;10µF 50V;C_1206_3216Metric_Pad1.33x1.80mm_HandSolder;
1;C3;22µF;C_1206_3216Metric_Pad1.33x1.80mm_HandSolder;
1;C4;10µF;C_0805_2012Metric_Pad1.18x1.45mm_HandSolder;
5;C5 C7 C8 C12 C13;100nF;C_0805_2012Metric_Pad1.18x1.45mm_HandSolder;
2;C6 C10;1µF;C_0805_2012Metric_Pad1.18x1.45mm_HandSolder;
1;C9;1µF 50V;C_0805_2012Metric_Pad1.18x1.45mm_HandSolder;
1;D1;SMBJ26A;D_SMB_Handsoldering;SMBJ26A
1;D2;12V;D_SOD-123;BZT52C12
1;D3;SS34;D_SMA_Handsoldering;SS34
1;F1;6.3A träge;Fuseholder_Clip-5x20mm_Bel_FC-203-22_Lateral_P17.80x5.00mm_D1.17mm_Horizontal;Sicherungshalter 5×20 + Feinsicherung T6,3A
1;J1;24V DC 5.5/2.1;BarrelJack_Horizontal;DC-Buchse 5,5/2,1 mm, ≥5 A
1;J4;USB-C;USB_C_Receptacle_GCT_USB4105-xx-A_16P_TopMnt_Horizontal;GCT USB4105-GF-A
1;J6;LED-Streifen 1;Kabel_4P_LED;
1;PS1;R-78E3.3-1.0;Converter_DCDC_RECOM_R-78E-0.5_THT;RECOM R-78E3.3-1.0 (oder R-783.3-1.0)
1;Q1;AOD4185;TO-252-2;AOD4185 (P-MOSFET −40 V)
1;R1;100k;R_0805_2012Metric_Pad1.20x1.40mm_HandSolder;
2;R4 R11;10k;R_0805_2012Metric_Pad1.20x1.40mm_HandSolder;
2;R5 R6;5.1k;R_0805_2012Metric_Pad1.20x1.40mm_HandSolder;
1;R7;120Ω;R_0805_2012Metric_Pad1.20x1.40mm_HandSolder;
2;R8 R9;680Ω;R_0805_2012Metric_Pad1.20x1.40mm_HandSolder;
1;R10;33Ω;R_0805_2012Metric_Pad1.20x1.40mm_HandSolder;
2;R12 R13;100Ω;R_0805_2012Metric_Pad1.20x1.40mm_HandSolder;
1;R14;5mΩ;R_2512_6332Metric_Pad1.40x3.35mm_HandSolder;Shunt 5 mΩ 2512 2 W
2;R15 R16;4.7k;R_0805_2012Metric_Pad1.20x1.40mm_HandSolder;
2;R17 R18;10Ω;R_0805_2012Metric_Pad1.20x1.40mm_HandSolder;
1;R19;10Ω;R_1206_3216Metric_Pad1.30x1.75mm_HandSolder;
1;SW1;BOOT;SW_PUSH_6mm;
1;SW2;RESET;SW_PUSH_6mm;
1;U2;78L05;SOT-89-3_Handsoldering;
1;U3;ESP32-S3-WROOM-1-N8R2;ESP32-S3-WROOM-1;ESP32-S3-WROOM-1 (N8R2 oder N16R8)
1;U4;MAX3485;SOIC-8_3.9x4.9mm_P1.27mm;MAX3485ESA / SP3485EN
1;U5;74AHCT1G125;SOT-23-5_HandSoldering;
1;U6;INA226;VSSOP-10_3x3mm_P0.5mm;INA226AIDGSR (I²C 0x40)
1;X2A;Kante 2 Pogo Stecker;Kabel_6P_Stecker;Magnet-Pogo 6-pol. männlich
1;X2B;Kante 2 Pogo Buchse;Kabel_6P_Buchse;Magnet-Pogo 6-pol. weiblich
1;X3A;Kante 3 Pogo Stecker;Kabel_6P_Stecker;Magnet-Pogo 6-pol. männlich
1;X3B;Kante 3 Pogo Buchse;Kabel_6P_Buchse;Magnet-Pogo 6-pol. weiblich
